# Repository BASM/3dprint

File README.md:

# 3dprint

Some experements for 3d printer

# copypaste for gitclone

git clone git@github.com:BASM/3dprint.git
git submodule init

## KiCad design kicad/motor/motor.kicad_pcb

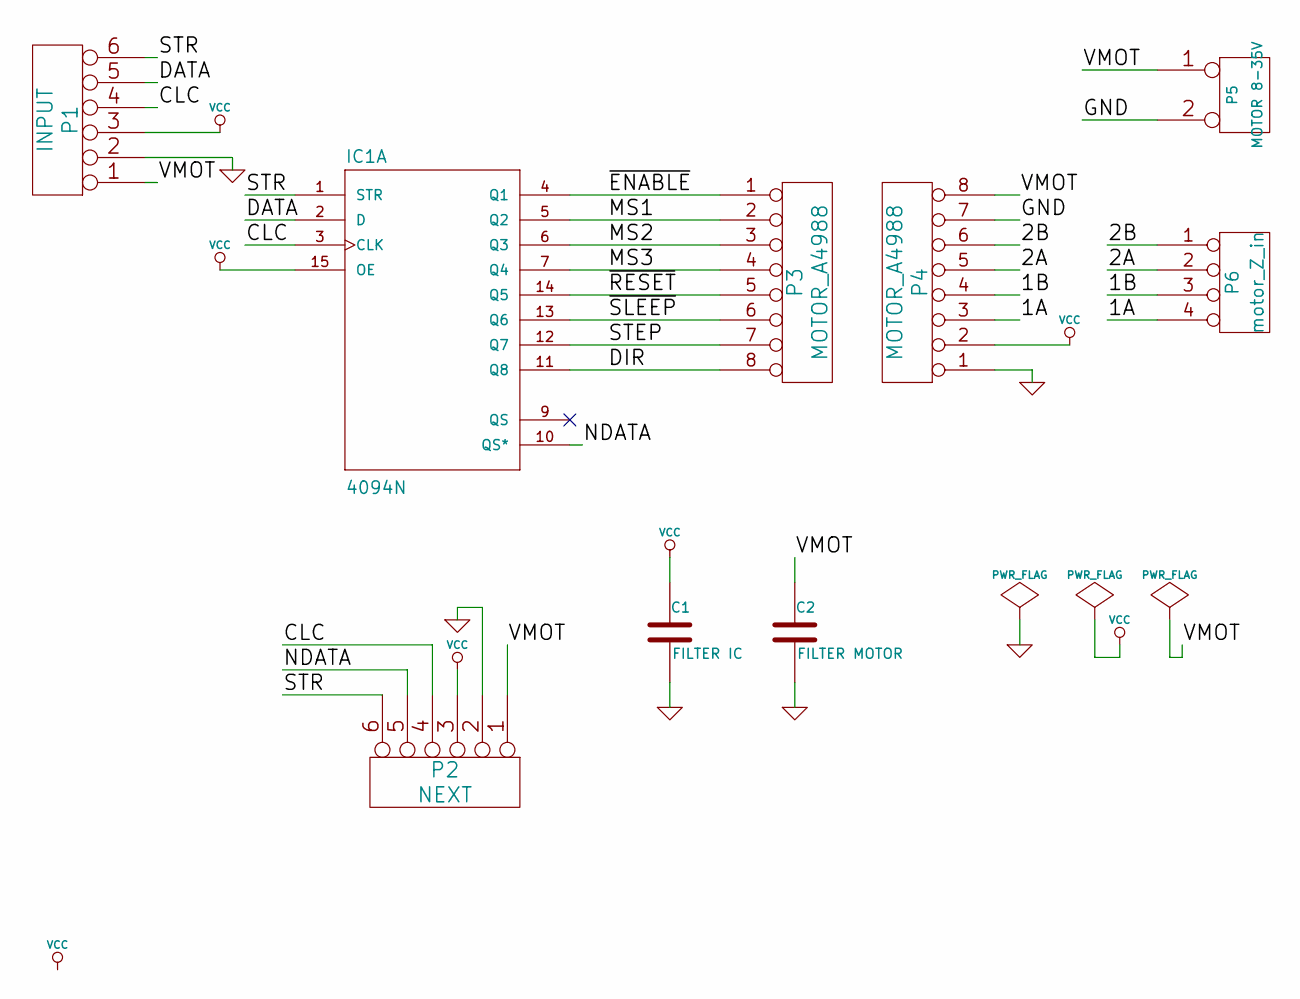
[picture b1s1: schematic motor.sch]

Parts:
C1: FILTER IC
C2: FILTER MOTOR
IC1: 4094N; 40xx-DIL16
P1: INPUT
P2: NEXT
P3, P4: MOTOR_A4988
P5: MOTOR 8-35V
P6: motor_Z_in

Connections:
/1A: P4.3, P6.4
/1B: P4.4, P6.3
/2A: P4.5, P6.2
/2B: P4.6, P6.1
/CLC: IC1.3 (CLK), P1.4, P2.4
/DATA: IC1.2 (D), P1.5
/DIR: IC1.11 (Q8), P3.8
/MS1: IC1.5 (Q2), P3.2
/MS2: IC1.6 (Q3), P3.3
/MS3: IC1.7 (Q4), P3.4
/NDATA: IC1.10 (QS*), P2.5
/STEP: IC1.12 (Q7), P3.7
/STR: IC1.1 (STR), P1.6, P2.6
/VMOT: C2.1, P1.1, P2.1, P4.8, P5.1
/~ENABLE: IC1.4 (Q1), P3.1
/~RESET: IC1.14 (Q5), P3.5
/~SLEEP: IC1.13 (Q6), P3.6
GND: C1.2, C2.2, P1.2, P2.2, P4.1, P4.7, P5.2 (PM)
VCC: C1.1, IC1.15 (OE), P1.3, P2.3, P4.2

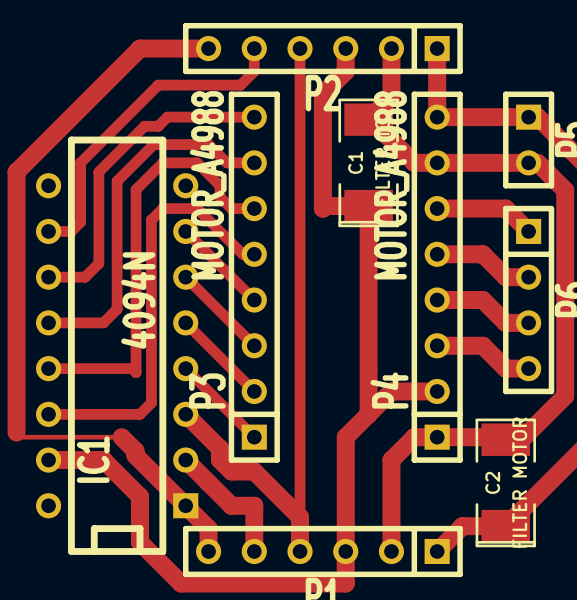
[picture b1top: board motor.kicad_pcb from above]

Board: 2 copper layers, 9 parts (0 on the bottom side), 19 nets.

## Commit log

2016-02-27 Added readme.md
2016-02-27 Added one serial motor board driver.
2016-02-27 Some small fix
2016-06-28 coffe
2016-06-28 First version
2016-06-29 Бороздка
2016-07-05 Fixed coffe
2016-07-13 Turtle
2016-07-13 Slicer config
2016-07-13 Fixed turtle
2017-02-01 Toy rings (and earrings) and rollers (for clothes dryer) models added.
